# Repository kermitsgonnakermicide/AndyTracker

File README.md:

# AndyTracker

**Intro**<br>
This is probably one of the _silliest_ projects I've ever worked on, but also one of the most FUN projects i've ever worked on<br>

A couple weeks ago, me and @TTF-fog met [Professor Andy Ruina](http://ruina.org/) at a summer program. We then learnt of his _strange_ approach to privacy, which was to ignore it. He wanted to share his location, 24/7 on his website, something which(thanks to us) is now up at https://ruina.org/location.html<br>

We then had the brilliant(read: stupid) idea of making a device that pointed at him 24/7, leading to this monstrosity

**Design**<br>
This is structured like any 2 axis pan/tilt mechanism, with the blue mini steppers. We did consider using servoes but honestly, we were so bored of using servoes that we decided to use these instead<br>
We also made a small carrier board for the ESP and the motor drivers, along with an OLED and MPU mounting point<br>

<br>
<br>

**BOM**<br>
| [S.NO](http://s.no/) | ITEM              | QTY | SOURCE                                                                                                                                                                                                                                                                 | Price               | Total  | NOTE                                 |
| -------------------- | ----------------- | --- | ---------------------------------------------------------------------------------------------------------------------------------------------------------------------------------------------------------------------------------------------------------------------- | ------------------- | ------ | ------------------------------------ |
| 1                    | XiaoESP32C3       | 1   | [https://sharvielectronics.com/product/seeed-studio-xiao-esp32c3-tiny-mcu-board-with-wifi-and-ble-battery-charge-supported-module/](https://sharvielectronics.com/product/seeed-studio-xiao-esp32c3-tiny-mcu-board-with-wifi-and-ble-battery-charge-supported-module/) | 7.34(including GST) | 7.34$  |                                      |
| 2                    | ULN2003 Driver    | 2   | [https://www.amazon.in/dp/B09NJLNKHQ?psc=1&ref_=cm_sw_r_cp_ud_ct_57NYJAS8ZS2QP6ZPSX17_2](https://www.amazon.in/dp/B09NJLNKHQ?psc=1&ref_=cm_sw_r_cp_ud_ct_57NYJAS8ZS2QP6ZPSX17_2)                                                                                       | 2.58                | 5.16   |                                      |
| 3                    | 28-BYJ-48 Stepper | 2   | [https://www.amazon.in/dp/B073Q2N6S7?psc=1&ref_=cm_sw_r_cp_ud_ct_57NYJAS8ZS2QP6ZPSX17_3](https://www.amazon.in/dp/B073Q2N6S7?psc=1&ref_=cm_sw_r_cp_ud_ct_57NYJAS8ZS2QP6ZPSX17_3)                                                                                       | 5.61                | 11.22  |                                      |
| 4                    | OLED - 128x64     | 1   | [https://www.amazon.in/dp/B07Q7VZ716?psc=1&ref_=cm_sw_r_cp_ud_ct_57NYJAS8ZS2QP6ZPSX17_4](https://www.amazon.in/dp/B07Q7VZ716?psc=1&ref_=cm_sw_r_cp_ud_ct_57NYJAS8ZS2QP6ZPSX17_4)                                                                                       | 4.38                | 4.38   |                                      |
| 5                    | IMU               | 1   | [https://www.amazon.in/dp/B0DWXXCPS9?psc=1&ref_=cm_sw_r_cp_ud_ct_57NYJAS8ZS2QP6ZPSX17_5](https://www.amazon.in/dp/B0DWXXCPS9?psc=1&ref_=cm_sw_r_cp_ud_ct_57NYJAS8ZS2QP6ZPSX17_5)                                                                                       | 3.54                | 3.54   |                                      |
| 6                    | PCB               | 1   | [https://www.seeedstudio.com/fusion_pcb.html](https://www.seeedstudio.com/fusion_pcb.html)                                                                                                                                                                             | 20                  | 20     | Roughly what it cost for my last pcb |
|                      |                   |     |                                                                                                                                                                                                                                                                        |                     | 51.64$ |                                      |

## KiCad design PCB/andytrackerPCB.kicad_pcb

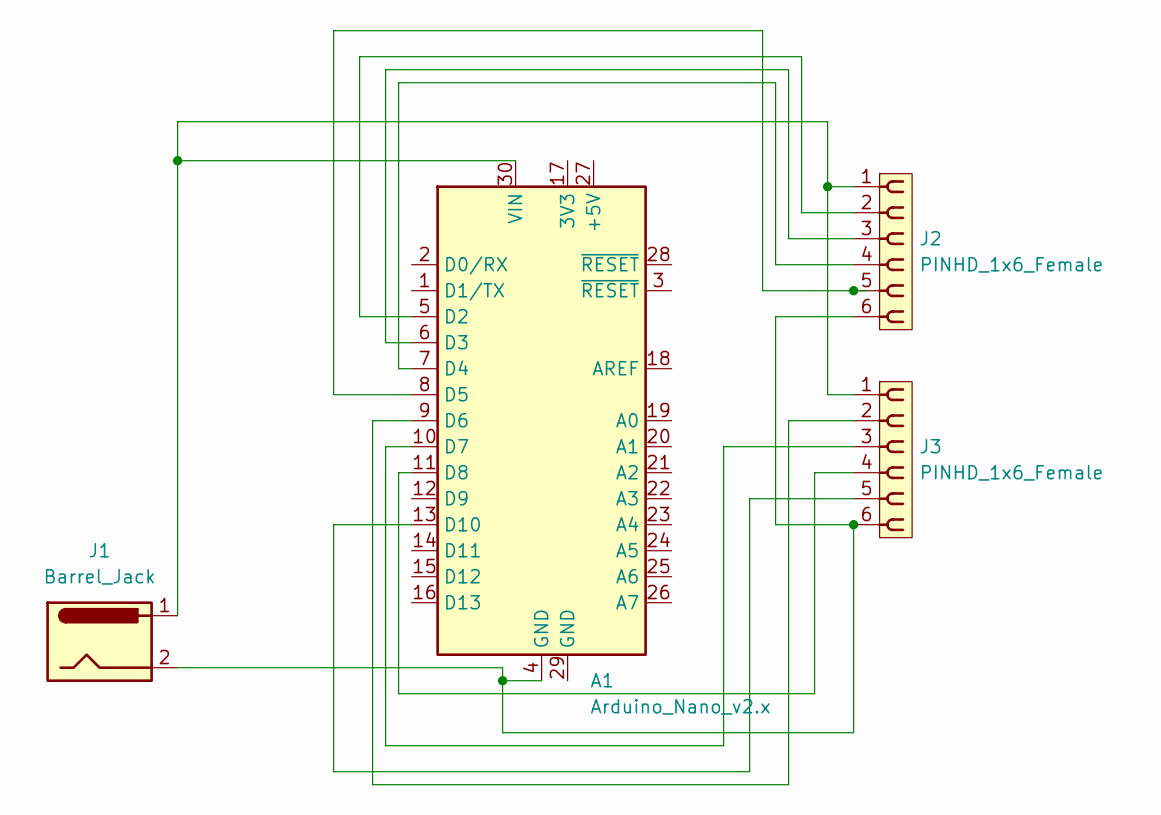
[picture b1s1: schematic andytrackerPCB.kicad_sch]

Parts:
A1: Arduino_Nano_v2.x; Arduino_Nano
J1: Barrel_Jack; BarrelJack_Horizontal
J2, J3: PINHD_1x6_Female; PinSocket_1x06_P2.54mm_Vertical

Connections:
unnamed: A1.5 (D2), J2.2
unnamed: A1.6 (D3), J2.3
unnamed: A1.7 (D4), J2.4
unnamed: A1.8 (D5), J2.5
unnamed: A1.9 (D6), J3.2
unnamed: A1.10 (D7), J3.3
unnamed: A1.11 (D8), J3.4
unnamed: A1.13 (D10), J3.5
unnamed: A1.4 (GND), J1.2, J2.6, J3.6
unnamed: A1.30 (VIN), J1.1, J2.1, J3.1

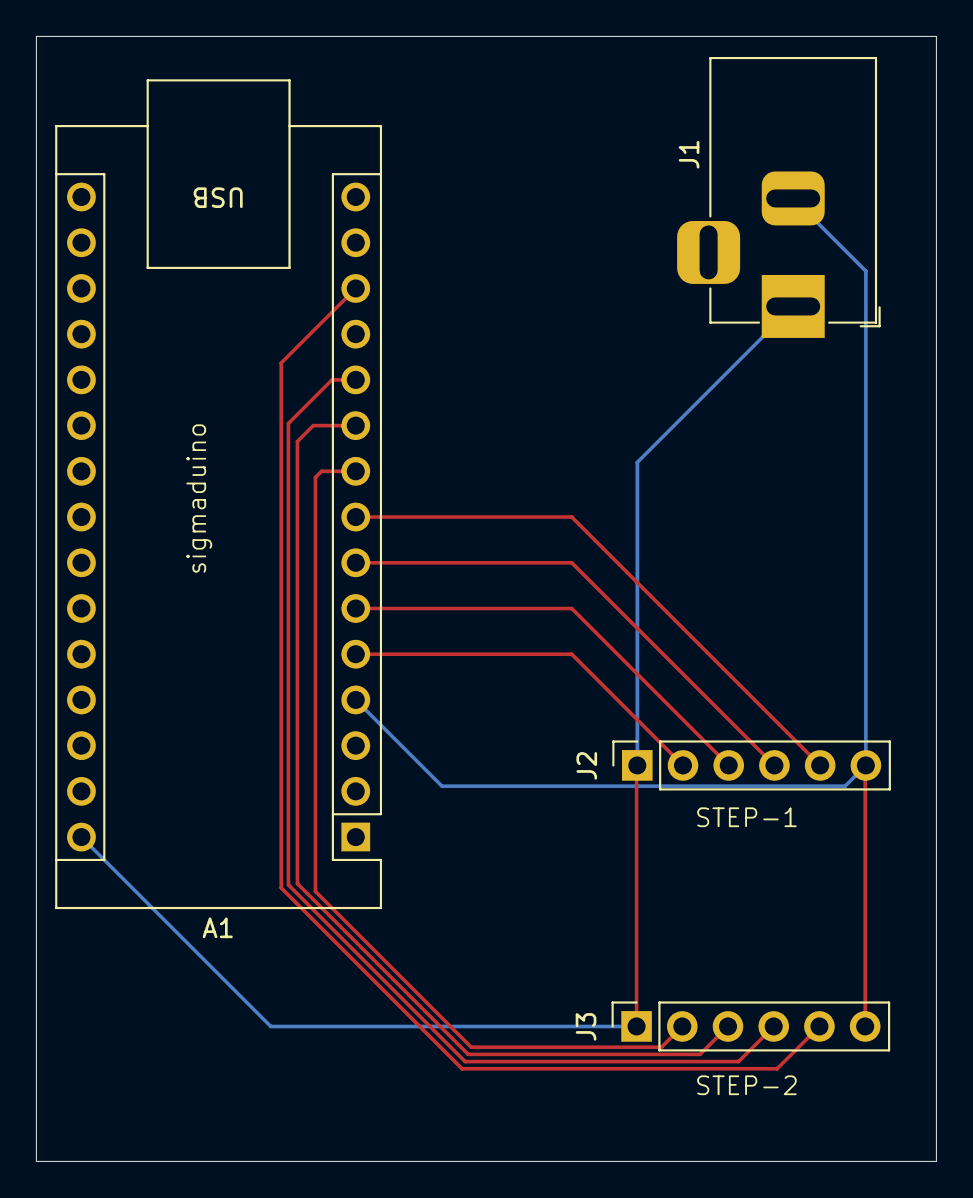
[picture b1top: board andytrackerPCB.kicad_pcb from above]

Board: 2 copper layers, 50.0 x 62.5 mm, 4 parts (0 on the bottom side), 10 nets.

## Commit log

2025-06-02 initial woohoo!!
2025-06-03 commit2
2025-06-04 final??
2025-06-10 some updates yeay
2025-06-10 updateswoohoo!!
2025-06-10 forgor to change image
2025-06-13 my journal isnt detailed?? i dont get that
2026-03-02 cleanup
    Updated formatting and added line breaks in the README.
